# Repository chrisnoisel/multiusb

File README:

sockets :
USB A
USB mini
USB micro

plugs :
USB A
USB B
USB mini
USB micro
USB mini OTG
USB micro OTG

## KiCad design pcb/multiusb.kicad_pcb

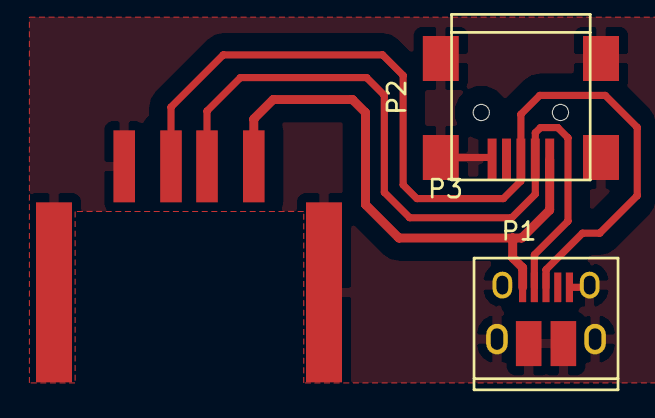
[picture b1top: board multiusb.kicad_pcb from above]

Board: 2 copper layers, 3 parts (0 on the bottom side), 4 nets.

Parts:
P1: USB_MICRO_OTG; USB_Micro-B_10103594-0001LF
P2: USB_MINI_OTG; USB_Mini-B
P3: USB_A

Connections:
/D+: P1.3, P2.3, P3.3
/D-: P1.2, P2.2, P3.2
/GND: P1.5, P1.6, P2.5, P2.6, P3.4, P3.5
/VCC: P1.1, P2.1, P3.1

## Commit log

2016-12-11 basic schema and pcb layout
2016-12-12 updated USB A footprint
2016-12-13 getting close to the final pcb layout
2016-12-24 wider tracks, push and shove tool test
